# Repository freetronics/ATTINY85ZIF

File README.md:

Freetronics ATtiny85 AVR ZIF Breakout
===================================
Copyright 2017 Freetronics Pty Ltd  
Freetronics site:  www.freetronics.com  
Freetronics email: info@freetronics.com  

Breakout for a ZIF (Zero Insertion Force) socket for ATtiny85 AVR microcontrollers,
with a header for ICSP.

Features:

 * 14-pin ZIF socket (use only part of the socket)
 * Header for 6-pin ICSP cable
 * Power LED
 * Reset button

More information is available at:

  http://www.freetronics.com/attiny85zif

INSTALLATION
------------
The design is saved as an EAGLE project. EAGLE PCB design software is
available from www.cadsoftusa.com free for non-commercial use. To use
this project download it and place the directory containing these files
into the "eagle" directory on your computer.

DISTRIBUTION
------------
The specific terms of distribution of this project are governed by the
license referenced below.

LICENSE
-------
Licensed under the TAPR Open Hardware License (www.tapr.org/OHL).
The "license" folder within this repository also contains a copy of
this license in plain text format.

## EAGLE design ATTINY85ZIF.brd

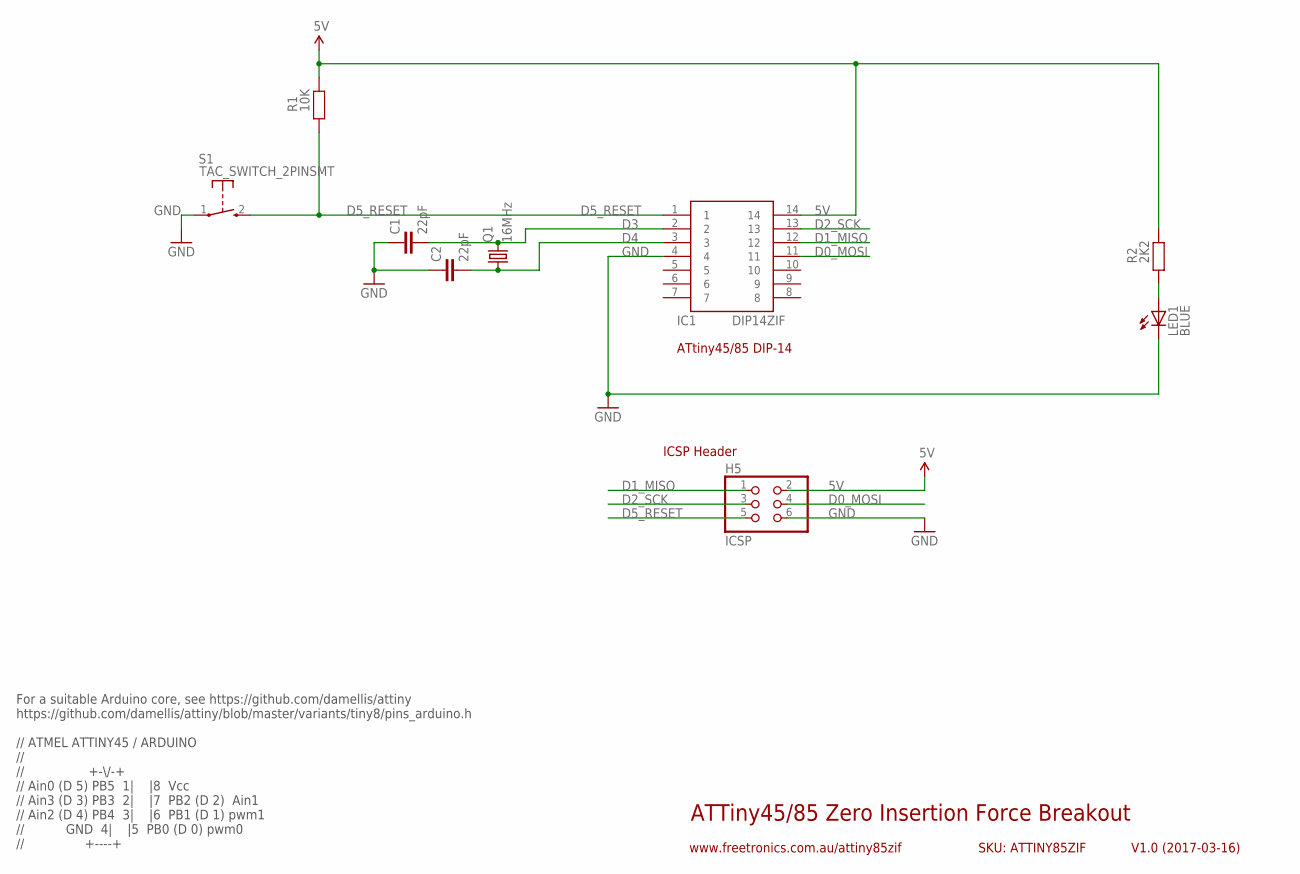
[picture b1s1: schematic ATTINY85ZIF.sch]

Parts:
C1, C2: 22pF; 0603
H5: ICSP; 2X03
IC1: DIP14ZIF; DIL14-3-ZIF
LED1: BLUE; LED-0603
Q1: 16MHz; HC49US
R1: 10K; 0603
R2: 2K2; 0603
S1: TAC_SWITCH_2PINSMT; TACTILE_SWITCH_SMD_2PIN_TINY

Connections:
5V: H5.2, IC1.14, R1.2, R2.2
D0_MOSI: H5.4, IC1.11
D1_MISO: H5.1, IC1.12
D2_SCK: H5.3, IC1.13
D3: C1.2, IC1.2, Q1.2
D4: C2.2, IC1.3, Q1.1
D5_RESET: H5.5, IC1.1, R1.1, S1.2 (S)
GND: C1.1, C2.1, H5.6, IC1.4, LED1.C, S1.1
unnamed: LED1.A, R2.1

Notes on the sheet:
ATTiny45/85 Zero Insertion Force Breakout
V1.0 (2017-03-16)
SKU: ATTINY85ZIF
www.freetronics.com.au/attiny85zif
ATtiny45/85 DIP-14
ICSP Header
For a suitable Arduino core, see https://github.com/damellis/attiny https://github.com/damellis/attiny/blob/master/variants/tiny8/pins_arduino.h // ATMEL ATTINY45 / ARDUINO // // +-\/-+ // Ain0 (D 5) PB5 1| |8 Vcc // Ain3 (D 3) PB3 2| |7 PB2 (D 2) Ain1 // Ain2 (D 4) PB4 3| |6 PB1 (D 1) pwm1 // GND 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

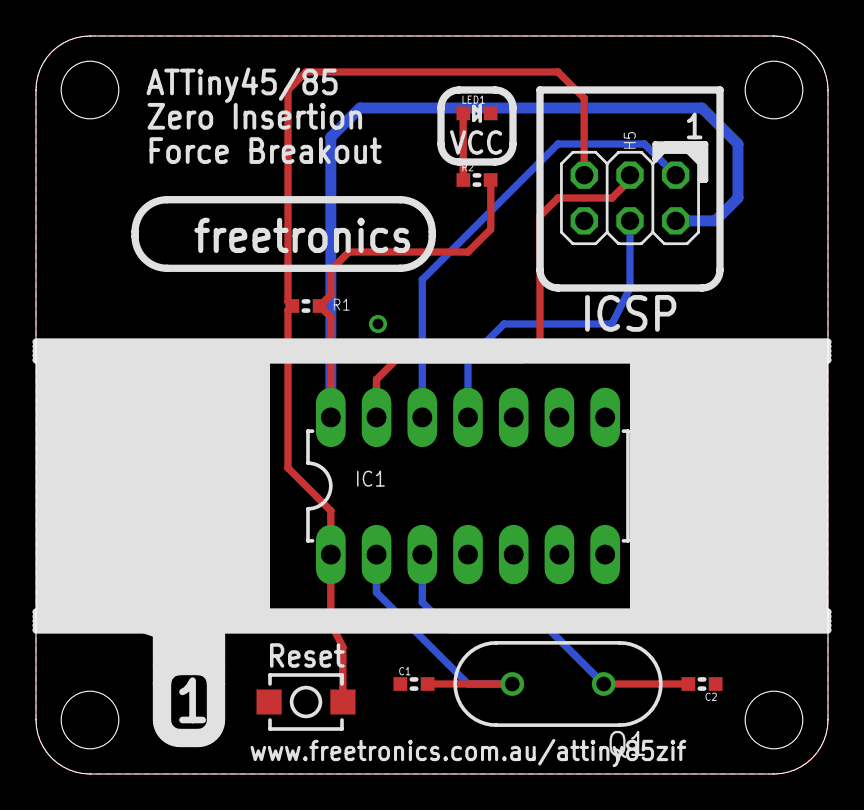
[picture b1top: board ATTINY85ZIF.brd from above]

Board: 2 copper layers, 44.0 x 41.0 mm, 9 parts (0 on the bottom side), 9 nets.

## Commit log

2018-03-22 Imported old project from April 2017

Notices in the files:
ATTINY85ZIF.brd:
(C)2017 Freetronics Pty Ltd
